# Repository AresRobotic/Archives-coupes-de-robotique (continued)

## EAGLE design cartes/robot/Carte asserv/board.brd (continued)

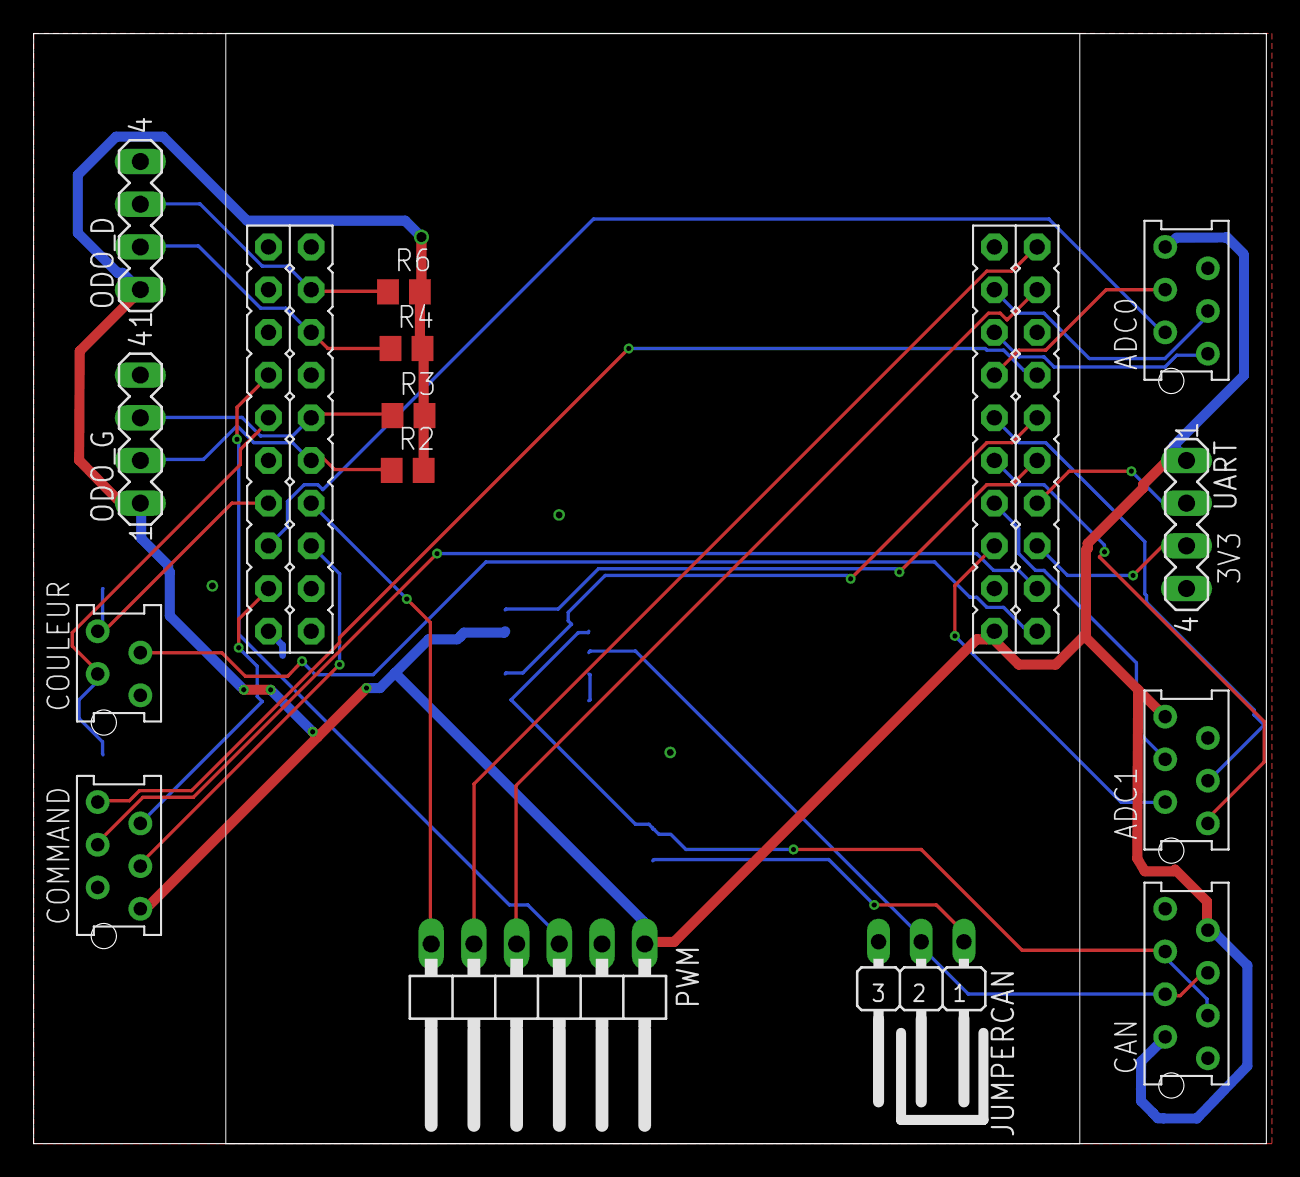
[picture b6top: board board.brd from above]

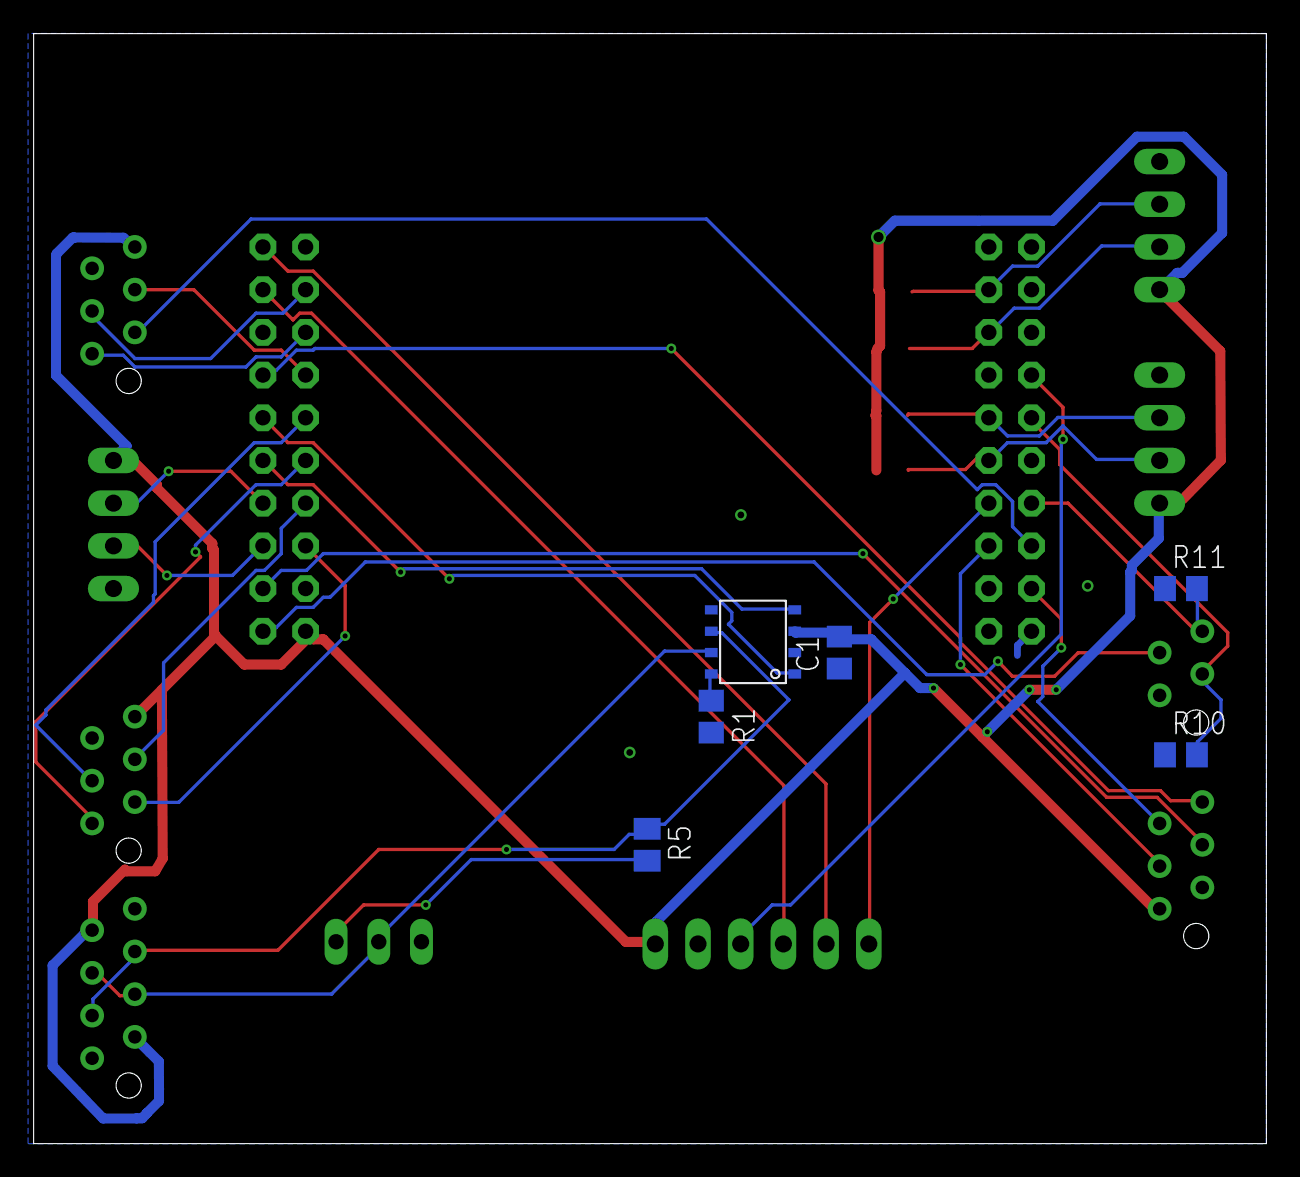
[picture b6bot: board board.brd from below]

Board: 2 copper layers, 73.3 x 66.0 mm, 21 parts (6 on the bottom side), 33 nets.
